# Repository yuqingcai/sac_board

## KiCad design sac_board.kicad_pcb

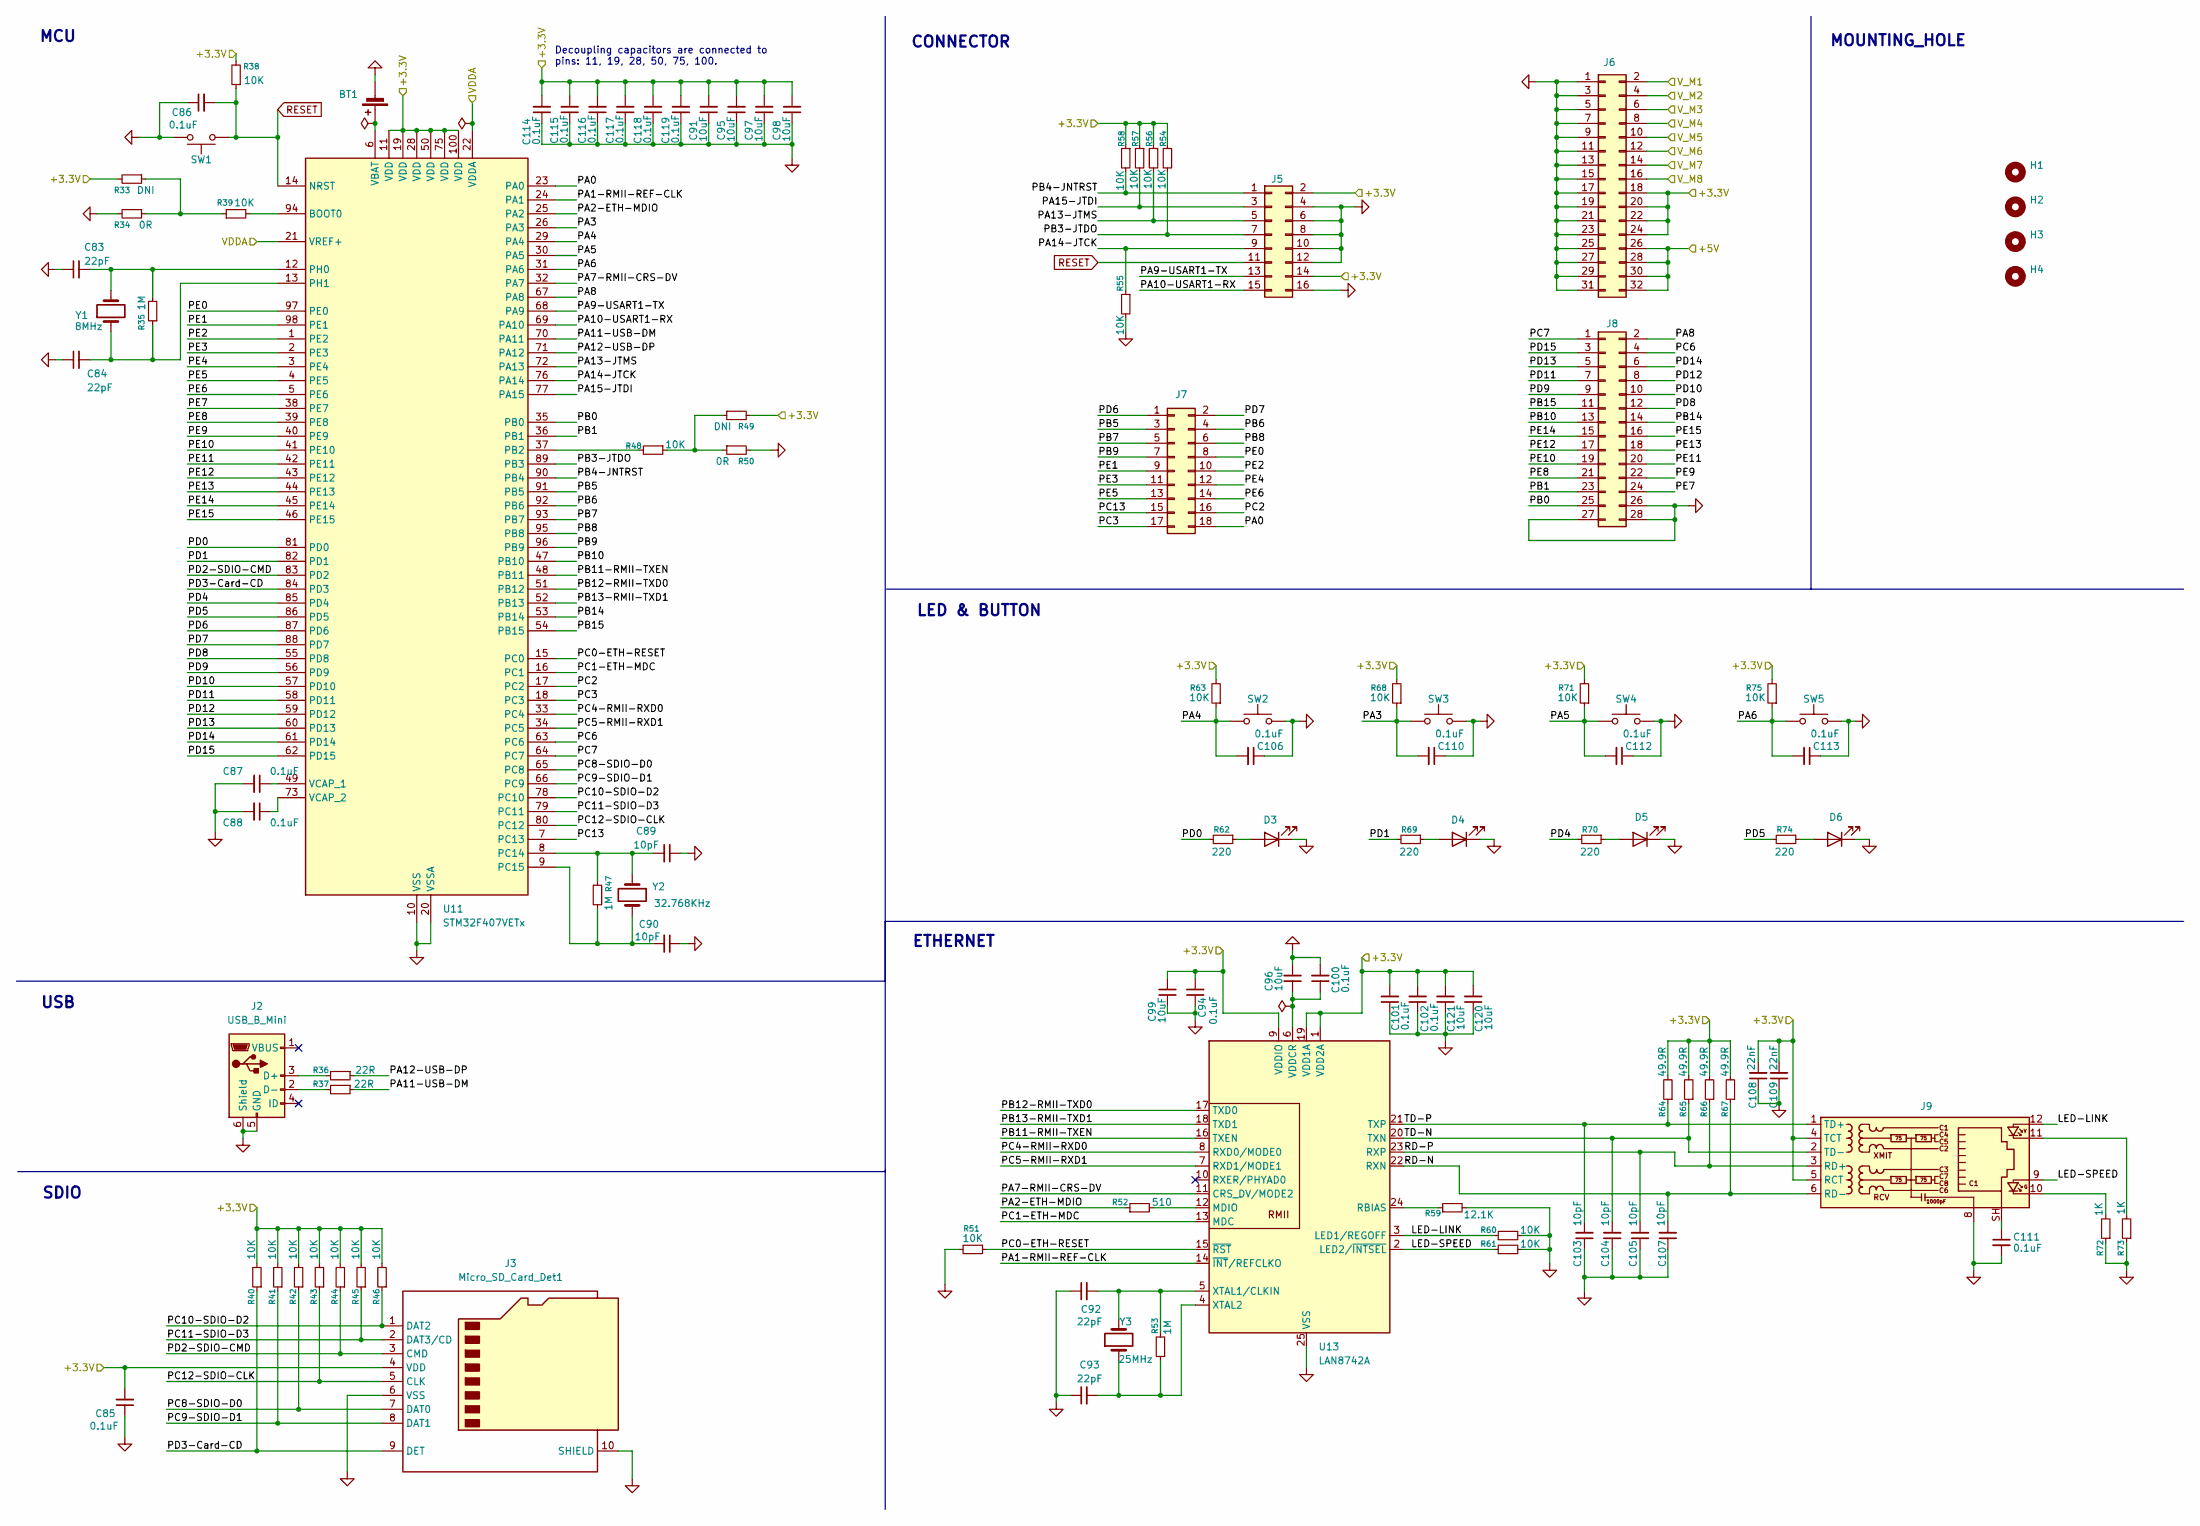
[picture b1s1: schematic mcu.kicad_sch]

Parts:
BT1: Battery_Cell; Battery_Panasonic_CR1220-VCN_Vertical_CircularHoles
C83, C84, C92, C93: 22pF; C_0805_2012Metric
C85, C86, C87, C88, C94, C100, C101, C102, C106, C110, C111, C112, C113, C114, C115, C116, C117, C118, C119: 0.1uF; C_0805_2012Metric
C89, C90, C103, C104, C105, C107: 10pF; C_0805_2012Metric
C91, C95, C96, C97, C98, C99, C120, C121: 10uF; C_0805_2012Metric
C108, C109: 22nF; C_0805_2012Metric
D3, D4: WHITE LED; LED_0805_2012Metric
D5, D6: ORANGE LED; LED_0805_2012Metric
H1, H2, H3, H4: MountingHole; MountingHole_3.2mm_M3
J2: USB_B_Mini; USB_Mini-B_Wuerth_65100516121_Horizontal
J3: Micro_SD_Card_Det1; microSD_HC_Hirose_DM3AT-SF-PEJM5
J5: Conn_02x08_Odd_Even; PinHeader_2x08_P2.54mm_Vertical
J6: Conn_02x16_Odd_Even; PinHeader_2x16_P2.54mm_Vertical
J7: Conn_02x09_Odd_Even; PinHeader_2x09_P2.54mm_Vertical
J8: Conn_02x14_Odd_Even; PinHeader_2x14_P2.54mm_Vertical
J9: RJ45; RJ45_Hanrun_HR911105A_Horizontal
R33, R49: DNI; R_0805_2012Metric
R34, R50: 0R; R_0805_2012Metric
R35, R47, R53: 1M; R_0805_2012Metric
R36, R37: 22R; R_0805_2012Metric
R38, R39, R40, R41, R42, R43, R44, R45, R46, R48, R51, R54, R55, R56, R57, R58, R60, R61, R63, R68, R71, R75: 10K; R_0805_2012Metric
R52: 510; R_0805_2012Metric
R59: 12.1K; R_0805_2012Metric
R62, R69, R70, R74: 220; R_0805_2012Metric
R64, R65, R66, R67: 49.9R; R_0805_2012Metric
R72, R73: 1K; R_0805_2012Metric
SW1, SW2, SW3, SW4, SW5: SW_Push_1P1T_NO_CK_KSC7xxJ
U11: STM32F407VETx; LQFP-100_14x14mm_P0.5mm
U13: LAN8742A; VQFN-24-1EP_4x4mm_P0.5mm_EP2.5x2.5mm
Y1: 8MHz; Crystal_SMD_5032-2Pin_5.0x3.2mm
Y2: 32.768KHz; Crystal_SMD_3215-2Pin_3.2x1.5mm
Y3: 25MHz; Crystal_SMD_5032-2Pin_5.0x3.2mm

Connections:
/mcu/+3.3V: C85.2, C91.2, C94.2, C95.2, C97.2, C98.2, C99.2, C101.2, C102.2, C108.2, C109.2, C114.2, C115.2, C116.2, C117.2, C118.2, C119.2, C120.2, C121.2, J3.4 (VDD), J5.2, J5.14, J6.18, J6.20, J6.22, J6.24, J9.4 (TCT), J9.5 (RCT), R33.2, R38.2, R40.2, R41.2, R42.2, R43.2, R44.2, R45.2, R46.2, R49.2, R54.1, R56.1, R57.1, R58.1, R63.2, R64.2, R65.2, R66.2, R67.2, R68.2, R71.2, R75.2, U11.11 (VDD), U11.19 (VDD), U11.28 (VDD), U11.50 (VDD), U11.75 (VDD), U11.100 (VDD), U13.1 (VDD2A), U13.9 (VDDIO), U13.19 (VDD1A); also elsewhere on the board
/mcu/+5V: J6.26, J6.28, J6.30, J6.32; also elsewhere on the board
/mcu/LED-LINK: J9.12, R60.1, U13.3 (LED1/REGOFF)
/mcu/LED-SPEED: J9.9, R61.1, U13.2 (LED2/~INTSEL)
/mcu/PA0: J7.18, U11.23 (PA0)
/mcu/PA1-RMII-REF-CLK: U11.24 (PA1), U13.14 (~INT/REFCLKO)
/mcu/PA2-ETH-MDIO: R52.1, U11.25 (PA2)
/mcu/PA3: C110.2, R68.1, SW3.1, U11.26 (PA3)
/mcu/PA4: C106.2, R63.1, SW2.1, U11.29 (PA4)
/mcu/PA5: C112.2, R71.1, SW4.1, U11.30 (PA5)
/mcu/PA6: C113.2, R75.1, SW5.1, U11.31 (PA6)
/mcu/PA7-RMII-CRS-DV: U11.32 (PA7), U13.11 (CRS_DV/MODE2)
/mcu/PA8: J8.2, U11.67 (PA8)
/mcu/PA9-USART1-TX: J5.13, U11.68 (PA9)
/mcu/PA10-USART1-RX: J5.15, U11.69 (PA10)
/mcu/PA11-USB-DM: R37.1, U11.70 (PA11)
/mcu/PA12-USB-DP: R36.1, U11.71 (PA12)
/mcu/PA13-JTMS: J5.5, R56.2, U11.72 (PA13)
/mcu/PA14-JTCK: J5.9, R55.1, U11.76 (PA14)
/mcu/PA15-JTDI: J5.3, R57.2, U11.77 (PA15)
/mcu/PB0: J8.25, U11.35 (PB0)
/mcu/PB1: J8.23, U11.36 (PB1)
/mcu/PB3-JTDO: J5.7, R54.2, U11.89 (PB3)
/mcu/PB4-JNTRST: J5.1, R58.2, U11.90 (PB4)
/mcu/PB5: J7.3, U11.91 (PB5)
/mcu/PB6: J7.4, U11.92 (PB6)
/mcu/PB7: J7.5, U11.93 (PB7)
/mcu/PB8: J7.6, U11.95 (PB8)
/mcu/PB9: J7.7, U11.96 (PB9)
/mcu/PB10: J8.13, U11.47 (PB10)
/mcu/PB11-RMII-TXEN: U11.48 (PB11), U13.16 (TXEN)
/mcu/PB12-RMII-TXD0: U11.51 (PB12), U13.17 (TXD0)
/mcu/PB13-RMII-TXD1: U11.52 (PB13), U13.18 (TXD1)
/mcu/PB14: J8.14, U11.53 (PB14)
/mcu/PB15: J8.11, U11.54 (PB15)
/mcu/PC0-ETH-RESET: R51.1, U11.15 (PC0), U13.15 (~RST)
/mcu/PC1-ETH-MDC: U11.16 (PC1), U13.13 (MDC)
/mcu/PC2: J7.16, U11.17 (PC2)
/mcu/PC3: J7.17, U11.18 (PC3)
/mcu/PC4-RMII-RXD0: U11.33 (PC4), U13.8 (RXD0/MODE0)
/mcu/PC5-RMII-RXD1: U11.34 (PC5), U13.7 (RXD1/MODE1)
/mcu/PC6: J8.4, U11.63 (PC6)
/mcu/PC7: J8.1, U11.64 (PC7)
/mcu/PC8-SDIO-D0: J3.7 (DAT0), R42.1, U11.65 (PC8)
/mcu/PC9-SDIO-D1: J3.8 (DAT1), R41.1, U11.66 (PC9)
/mcu/PC10-SDIO-D2: J3.1 (DAT2), R46.1, U11.78 (PC10)
/mcu/PC11-SDIO-D3: J3.2 (DAT3/CD), R45.1, U11.79 (PC11)
/mcu/PC12-SDIO-CLK: J3.5 (CLK), R43.1, U11.80 (PC12)
/mcu/PC13: J7.15, U11.7 (PC13)
/mcu/PD0: R62.2, U11.81 (PD0)
/mcu/PD1: R69.2, U11.82 (PD1)
/mcu/PD2-SDIO-CMD: J3.3 (CMD), R44.1, U11.83 (PD2)
/mcu/PD3-Card-CD: J3.9 (DET), R40.1, U11.84 (PD3)
/mcu/PD4: R70.2, U11.85 (PD4)
/mcu/PD5: R74.2, U11.86 (PD5)
/mcu/PD6: J7.1, U11.87 (PD6)
/mcu/PD7: J7.2, U11.88 (PD7)
/mcu/PD8: J8.12, U11.55 (PD8)
/mcu/PD9: J8.9, U11.56 (PD9)
/mcu/PD10: J8.10, U11.57 (PD10)
/mcu/PD11: J8.7, U11.58 (PD11)
/mcu/PD12: J8.8, U11.59 (PD12)
/mcu/PD13: J8.5, U11.60 (PD13)
/mcu/PD14: J8.6, U11.61 (PD14)
/mcu/PD15: J8.3, U11.62 (PD15)
/mcu/PE0: J7.8, U11.97 (PE0)
/mcu/PE1: J7.9, U11.98 (PE1)
/mcu/PE2: J7.10, U11.1 (PE2)
/mcu/PE3: J7.11, U11.2 (PE3)
/mcu/PE4: J7.12, U11.3 (PE4)
/mcu/PE5: J7.13, U11.4 (PE5)
/mcu/PE6: J7.14, U11.5 (PE6)
/mcu/PE7: J8.24, U11.38 (PE7)
/mcu/PE8: J8.21, U11.39 (PE8)
/mcu/PE9: J8.22, U11.40 (PE9)
/mcu/PE10: J8.19, U11.41 (PE10)
/mcu/PE11: J8.20, U11.42 (PE11)
/mcu/PE12: J8.17, U11.43 (PE12)
/mcu/PE13: J8.18, U11.44 (PE13)
/mcu/PE14: J8.15, U11.45 (PE14)
/mcu/PE15: J8.16, U11.46 (PE15)
/mcu/RD-N: C107.2, J9.6 (RD-), R67.1, U13.22 (RXN)
/mcu/RD-P: C105.2, J9.3 (RD+), R66.1, U13.23 (RXP)
/mcu/TD-N: C104.2, J9.2 (TD-), R65.1, U13.20 (TXN)
/mcu/TD-P: C103.2, J9.1 (TD+), R64.1, U13.21 (TXP)
/mcu/VDDA: U11.21 (VREF+), U11.22 (VDDA); also elsewhere on the board
/mcu/V_M1: J6.2; also elsewhere on the board
/mcu/V_M2: J6.4; also elsewhere on the board
/mcu/V_M3: J6.6; also elsewhere on the board
/mcu/V_M4: J6.8; also elsewhere on the board
/mcu/V_M5: J6.10; also elsewhere on the board
/mcu/V_M6: J6.12; also elsewhere on the board
/mcu/V_M7: J6.14; also elsewhere on the board
/mcu/V_M8: J6.16; also elsewhere on the board
GND: BT1.2 (-), C83.1, C84.1, C85.1, C86.1, C87.2, C88.2, C89.1, C90.1, C91.1, C92.1, C93.1, C94.1, C95.1, C96.2, C97.1, C98.1, C99.1, C100.2, C101.1, C102.1, C103.1, C104.1, C105.1, C106.1, C107.1, C108.1, C109.1, C110.1, C111.2, C112.1, C113.1, C114.1, C115.1, C116.1, C117.1, C118.1, C119.1, C120.1, C121.1, D3.1 (K), D4.1 (K), D5.1 (K), D6.1 (K), J2.5 (GND), J2.6 (Shield), J3.6 (VSS), J3.10 (SHIELD), J5.4, J5.6, J5.8, J5.10, J5.12, J5.16, J6.1, J6.3, J6.5, J6.7, J6.9, J6.11, J6.13, J6.15, J6.17, J6.19, J6.21, J6.23, J6.25, J6.27, J6.29, J6.31, J8.26, J8.27, J8.28, J9.8, R34.2, R50.2, R51.2, R55.2, R59.2, R60.2, R61.2, R72.1, R73.1, SW1.2, SW2.2, SW3.2, SW4.2, SW5.2, U11.10 (VSS), U11.20 (VSSA), U11.27 (VSS), U11.74 (VSS), U11.99 (VSS), U13.25 (VSS); also elsewhere on the board
unnamed: BT1.1 (+), U11.6 (VBAT)
unnamed: C111.1, J9.SH
unnamed: D3.2 (A), R62.1
unnamed: D4.2 (A), R69.1
unnamed: D5.2 (A), R70.1
unnamed: D6.2 (A), R74.1
unnamed: J2.3 (D+), R36.2
unnamed: J2.2 (D-), R37.2
unnamed: J9.10, R72.2
unnamed: J9.11, R73.2
unnamed: R33.1, R34.1, R39.1
unnamed: R48.1, R49.1, R50.1
unnamed: R39.2, U11.94 (BOOT0)
unnamed: R48.2, U11.37 (PB2)
unnamed: C89.2, R47.1, U11.8 (PC14), Y2.1
unnamed: C90.2, R47.2, U11.9 (PC15), Y2.2
unnamed: C83.2, R35.2, U11.12 (PH0), Y1.2
unnamed: C84.2, R35.1, U11.13 (PH1), Y1.1
unnamed: C87.1, U11.49 (VCAP_1)
unnamed: C88.1, U11.73 (VCAP_2)
unnamed: R52.2, U13.12 (MDIO)
unnamed: R59.1, U13.24 (RBIAS)
unnamed: C96.1, C100.1, U13.6 (VDDCR)
unnamed: C92.2, R53.2, U13.5 (XTAL1/CLKIN), Y3.2
unnamed: C93.2, R53.1, U13.4 (XTAL2), Y3.1
RESET: C86.2, J5.11, R38.1, SW1.1, U11.14 (NRST)

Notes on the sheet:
Decoupling capacitors are connected to pins: 11, 19, 28, 50, 75, 100.
ETHERNET
USB
SDIO
MCU
MOUNTING_HOLE
LED & BUTTON
CONNECTOR

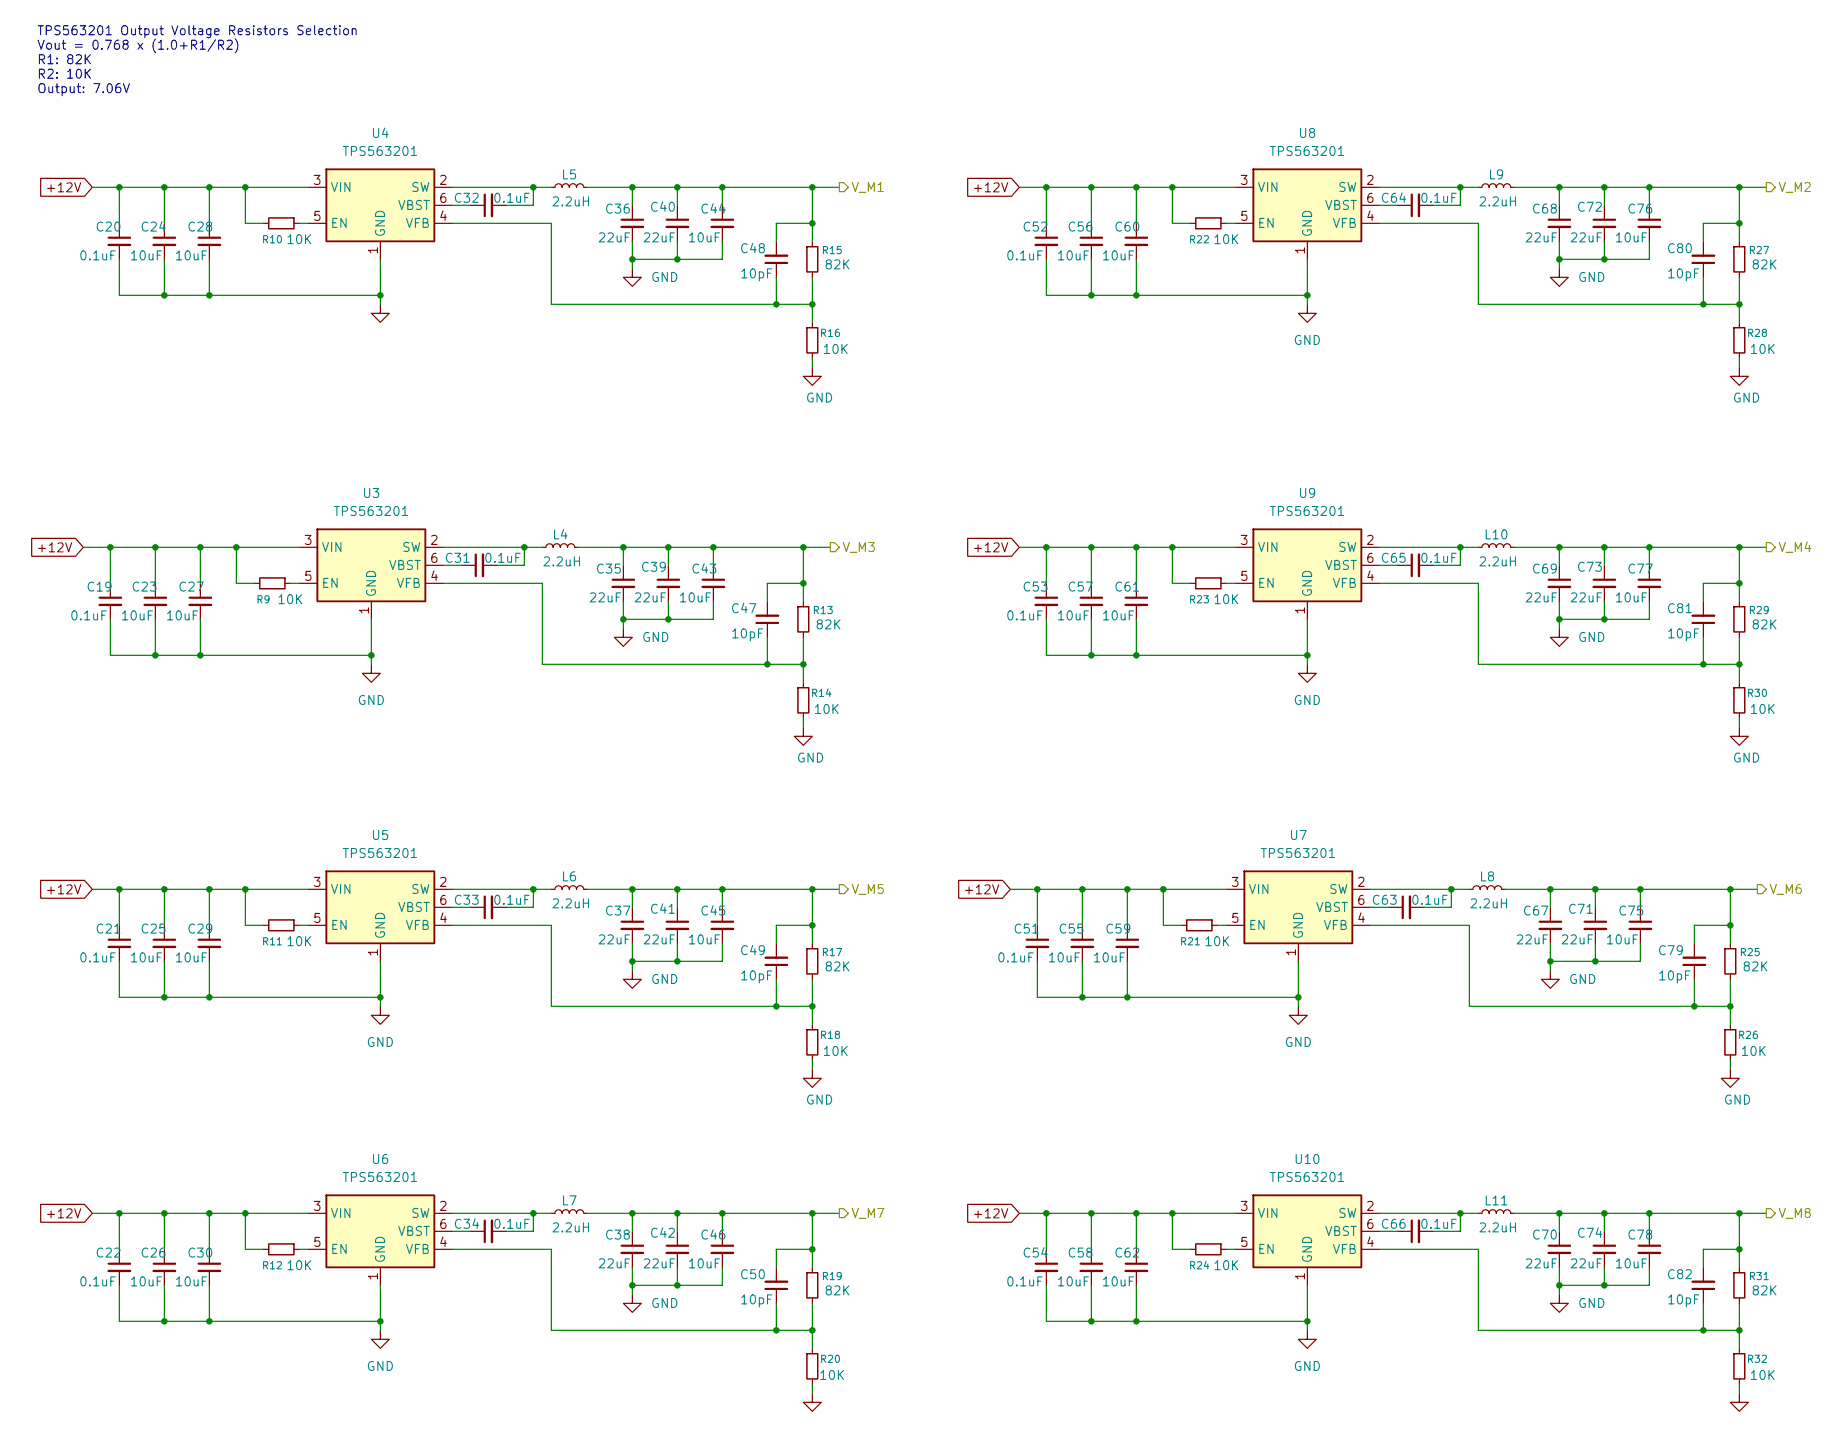
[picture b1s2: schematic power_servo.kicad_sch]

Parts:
C19, C20, C21, C22, C31, C32, C33, C34, C51, C52, C53, C54, C63, C64, C65, C66: 0.1uF; C_0805_2012Metric
C23, C24, C25, C26, C27, C28, C29, C30, C43, C44, C45, C46, C55, C56, C57, C58, C59, C60, C61, C62, C75, C76, C77, C78: 10uF; C_0805_2012Metric
C35, C36, C37, C38, C39, C40, C41, C42, C67, C68, C69, C70, C71, C72, C73, C74: 22uF; C_0805_2012Metric
C47, C48, C49, C50, C79, C80, C81, C82: 10pF; C_0805_2012Metric
L4, L5, L6, L7, L8, L9, L10, L11: 2.2uH; L_Changjiang_FXL0630
R9, R10, R11, R12, R14, R16, R18, R20, R21, R22, R23, R24, R26, R28, R30, R32: 10K; R_0805_2012Metric
R13, R15, R17, R19, R25, R27, R29, R31: 82K; R_0805_2012Metric
U3, U4, U5, U6, U7, U8, U9, U10: TPS563201; SOT-23-6

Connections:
+12V: C19.1, C20.1, C21.1, C22.1, C23.1, C24.1, C25.1, C26.1, C27.1, C28.1, C29.1, C30.1, C51.1, C52.1, C53.1, C54.1, C55.1, C56.1, C57.1, C58.1, C59.1, C60.1, C61.1, C62.1, R9.2, R10.2, R11.2, R12.2, R21.2, R22.2, R23.2, R24.2, U3.3 (VIN), U4.3 (VIN), U5.3 (VIN), U6.3 (VIN), U7.3 (VIN), U8.3 (VIN), U9.3 (VIN), U10.3 (VIN); also elsewhere on the board
/mcu/V_M1: C36.1, C40.1, C44.1, C48.2, L5.2, R15.1; also elsewhere on the board
/mcu/V_M2: C68.1, C72.1, C76.1, C80.2, L9.2, R27.1; also elsewhere on the board
/mcu/V_M3: C35.1, C39.1, C43.1, C47.2, L4.2, R13.1; also elsewhere on the board
/mcu/V_M4: C69.1, C73.1, C77.1, C81.2, L10.2, R29.1; also elsewhere on the board
/mcu/V_M5: C37.1, C41.1, C45.1, C49.2, L6.2, R17.1; also elsewhere on the board
/mcu/V_M6: C67.1, C71.1, C75.1, C79.2, L8.2, R25.1; also elsewhere on the board
/mcu/V_M7: C38.1, C42.1, C46.1, C50.2, L7.2, R19.1; also elsewhere on the board
/mcu/V_M8: C70.1, C74.1, C78.1, C82.2, L11.2, R31.1; also elsewhere on the board
GND: C19.2, C20.2, C21.2, C22.2, C23.2, C24.2, C25.2, C26.2, C27.2, C28.2, C29.2, C30.2, C35.2, C36.2, C37.2, C38.2, C39.2, C40.2, C41.2, C42.2, C43.2, C44.2, C45.2, C46.2, C51.2, C52.2, C53.2, C54.2, C55.2, C56.2, C57.2, C58.2, C59.2, C60.2, C61.2, C62.2, C67.2, C68.2, C69.2, C70.2, C71.2, C72.2, C73.2, C74.2, C75.2, C76.2, C77.2, C78.2, R14.2, R16.2, R18.2, R20.2, R26.2, R28.2, R30.2, R32.2, U3.1 (GND), U4.1 (GND), U5.1 (GND), U6.1 (GND), U7.1 (GND), U8.1 (GND), U9.1 (GND), U10.1 (GND); also elsewhere on the board
unnamed: R9.1, U3.5 (EN)
unnamed: C31.2, L4.1, U3.2 (SW)
unnamed: C31.1, U3.6 (VBST)
unnamed: C47.1, R13.2, R14.1, U3.4 (VFB)
unnamed: R10.1, U4.5 (EN)
unnamed: C32.2, L5.1, U4.2 (SW)
unnamed: C32.1, U4.6 (VBST)
unnamed: C48.1, R15.2, R16.1, U4.4 (VFB)
unnamed: R11.1, U5.5 (EN)
unnamed: C33.2, L6.1, U5.2 (SW)
unnamed: C33.1, U5.6 (VBST)
unnamed: C49.1, R17.2, R18.1, U5.4 (VFB)
unnamed: R12.1, U6.5 (EN)
unnamed: C34.2, L7.1, U6.2 (SW)
unnamed: C34.1, U6.6 (VBST)
unnamed: C50.1, R19.2, R20.1, U6.4 (VFB)
unnamed: R21.1, U7.5 (EN)
unnamed: C63.2, L8.1, U7.2 (SW)
unnamed: C63.1, U7.6 (VBST)
unnamed: C79.1, R25.2, R26.1, U7.4 (VFB)
unnamed: R22.1, U8.5 (EN)
unnamed: C64.2, L9.1, U8.2 (SW)
unnamed: C64.1, U8.6 (VBST)
unnamed: C80.1, R27.2, R28.1, U8.4 (VFB)
unnamed: R23.1, U9.5 (EN)
unnamed: C65.2, L10.1, U9.2 (SW)
unnamed: C65.1, U9.6 (VBST)
unnamed: C81.1, R29.2, R30.1, U9.4 (VFB)
unnamed: R24.1, U10.5 (EN)
unnamed: C66.2, L11.1, U10.2 (SW)
unnamed: C66.1, U10.6 (VBST)
unnamed: C82.1, R31.2, R32.1, U10.4 (VFB)

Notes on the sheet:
TPS563201 Output Voltage Resistors Selection Vout = 0.768 x (1.0+R1/R2) R1: 82K R2: 10K Output: 7.06V

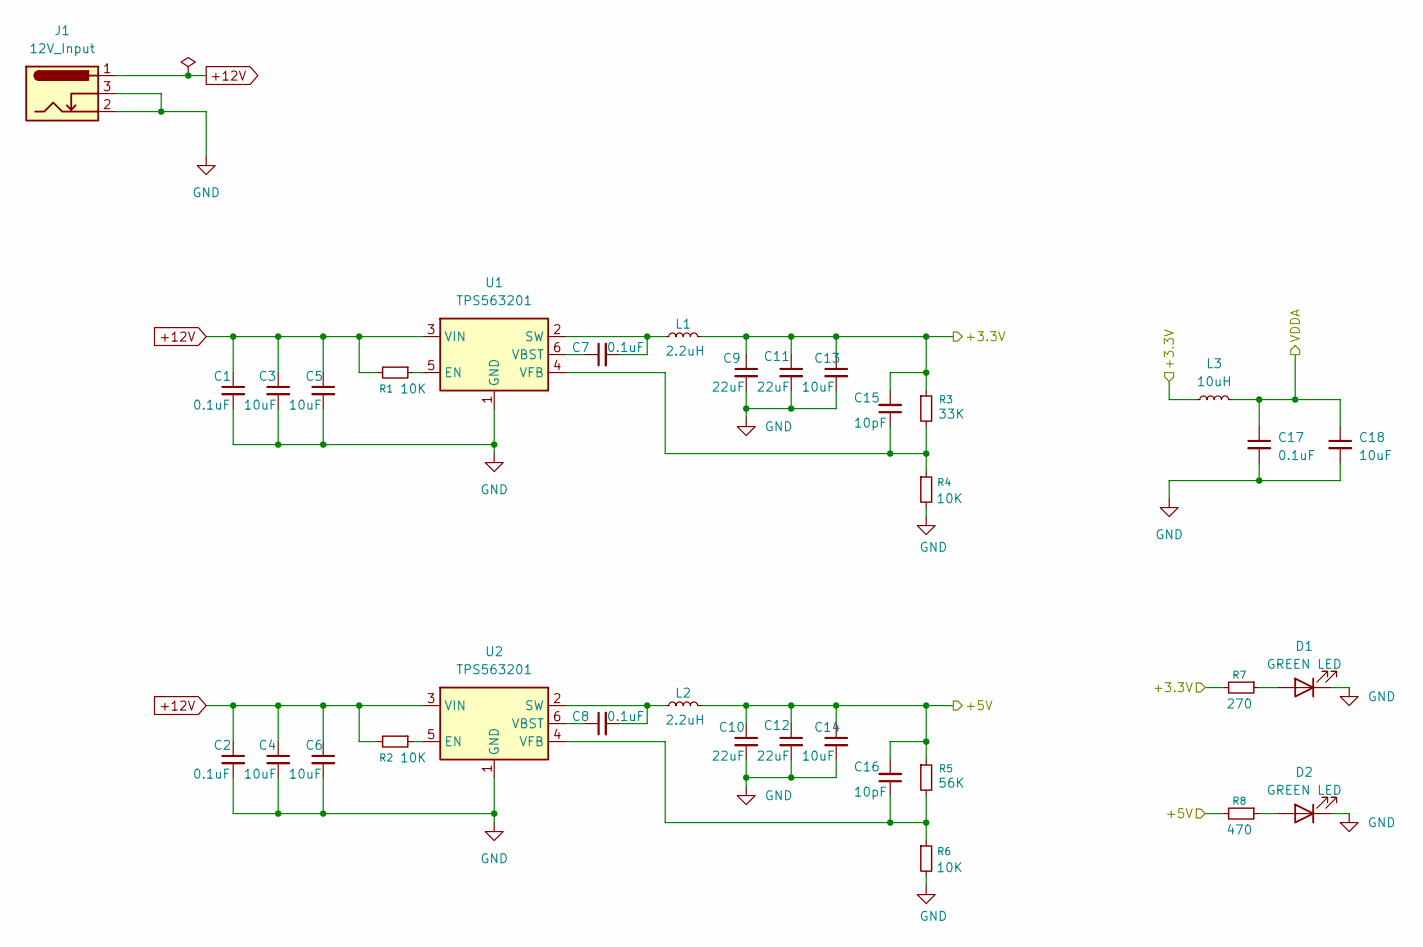
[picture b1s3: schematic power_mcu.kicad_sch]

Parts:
C1, C2, C7, C8, C17: 0.1uF; C_0805_2012Metric
C3, C4, C5, C6, C13, C14, C18: 10uF; C_0805_2012Metric
C9, C10, C11, C12: 22uF; C_0805_2012Metric
C15, C16: 10pF; C_0805_2012Metric
D1, D2: GREEN LED; LED_0805_2012Metric
J1: 12V_Input; BarrelJack_GCT_DCJ200-10-A_Horizontal
L1, L2: 2.2uH; L_Changjiang_FXL0630
L3: 10uH; L_0805_2012Metric
R1, R2, R4, R6: 10K; R_0805_2012Metric
R3: 33K; R_0805_2012Metric
R5: 56K; R_0805_2012Metric
R7: 270; R_0805_2012Metric
R8: 470; R_0805_2012Metric
U1, U2: TPS563201; SOT-23-6

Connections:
+12V: C1.1, C2.1, C3.1, C4.1, C5.1, C6.1, J1.1, R1.2, R2.2, U1.3 (VIN), U2.3 (VIN); also elsewhere on the board
/mcu/+3.3V: C9.1, C11.1, C13.1, C15.2, L1.2, L3.1, R3.1, R7.2; also elsewhere on the board
/mcu/+5V: C10.1, C12.1, C14.1, C16.2, L2.2, R5.1, R8.2; also elsewhere on the board
/mcu/VDDA: C17.1, C18.1, L3.2; also elsewhere on the board
GND: C1.2, C2.2, C3.2, C4.2, C5.2, C6.2, C9.2, C10.2, C11.2, C12.2, C13.2, C14.2, C17.2, C18.2, D1.1 (K), D2.1 (K), J1.2, J1.3, R4.2, R6.2, U1.1 (GND), U2.1 (GND); also elsewhere on the board
unnamed: D1.2 (A), R7.1
unnamed: D2.2 (A), R8.1
unnamed: R1.1, U1.5 (EN)
unnamed: C7.2, L1.1, U1.2 (SW)
unnamed: C7.1, U1.6 (VBST)
unnamed: C15.1, R3.2, R4.1, U1.4 (VFB)
unnamed: R2.1, U2.5 (EN)
unnamed: C8.2, L2.1, U2.2 (SW)
unnamed: C8.1, U2.6 (VBST)
unnamed: C16.1, R5.2, R6.1, U2.4 (VFB)

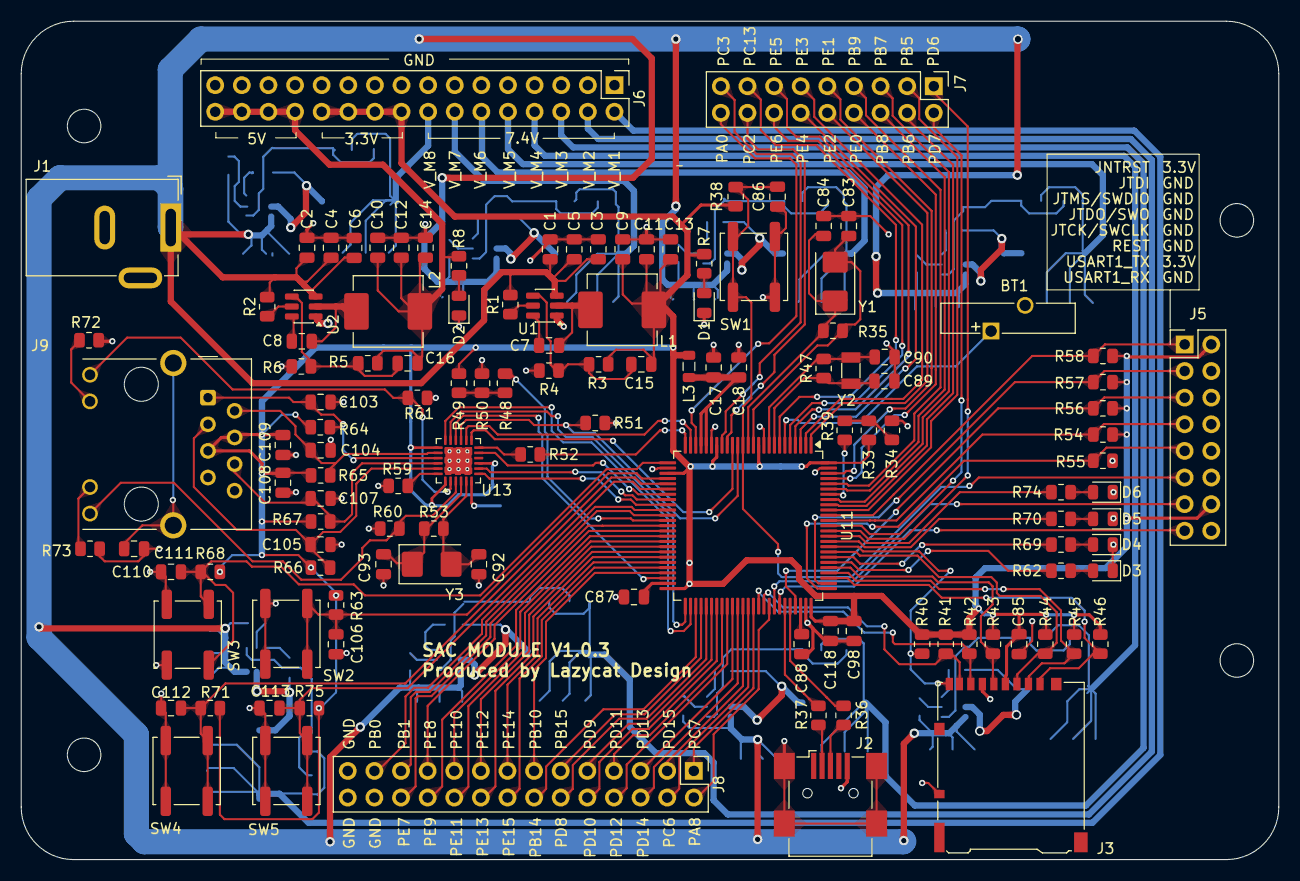
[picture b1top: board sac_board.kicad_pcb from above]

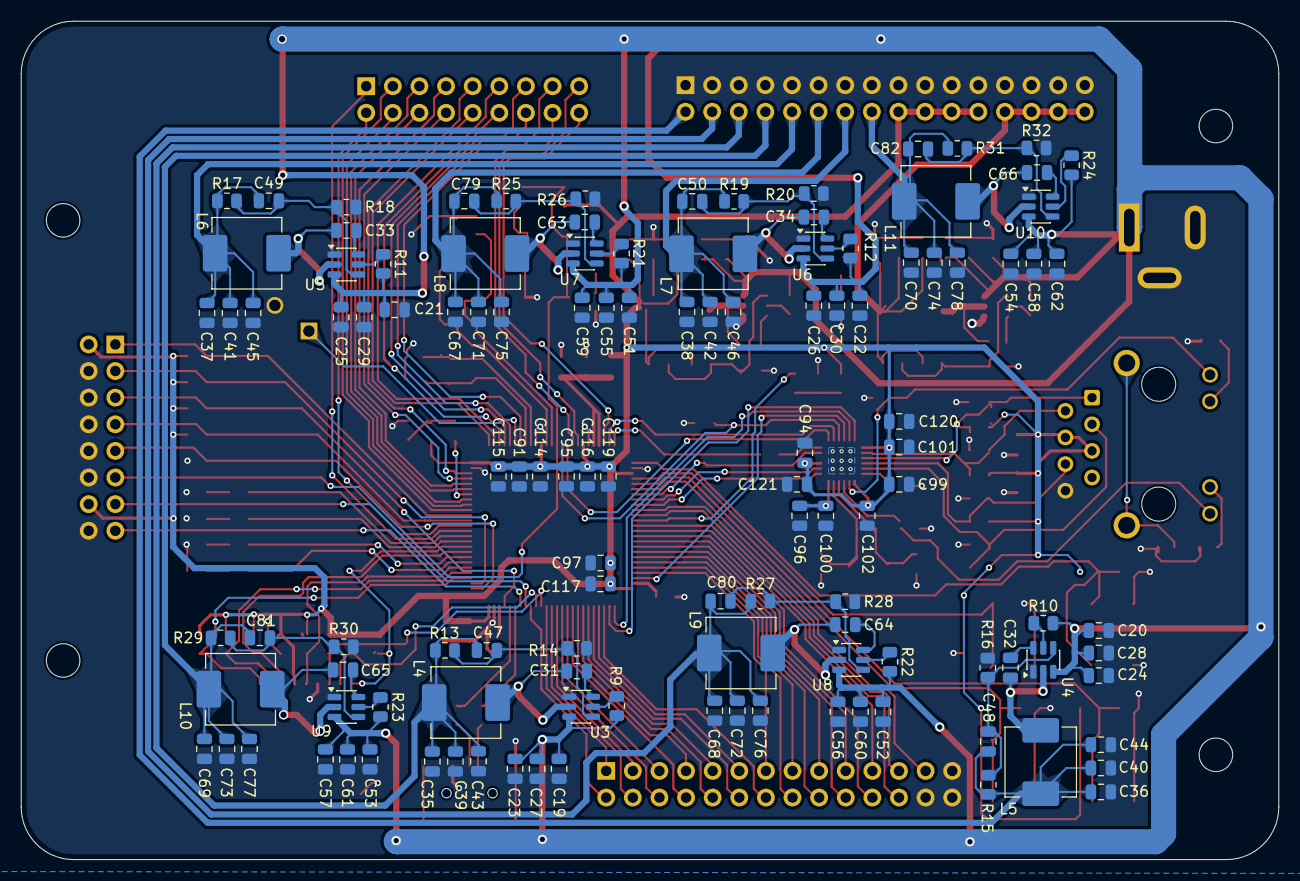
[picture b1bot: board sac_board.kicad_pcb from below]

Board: 2 copper layers, 120.0 x 80.0 mm, 246 parts (120 on the bottom side), 164 nets.
